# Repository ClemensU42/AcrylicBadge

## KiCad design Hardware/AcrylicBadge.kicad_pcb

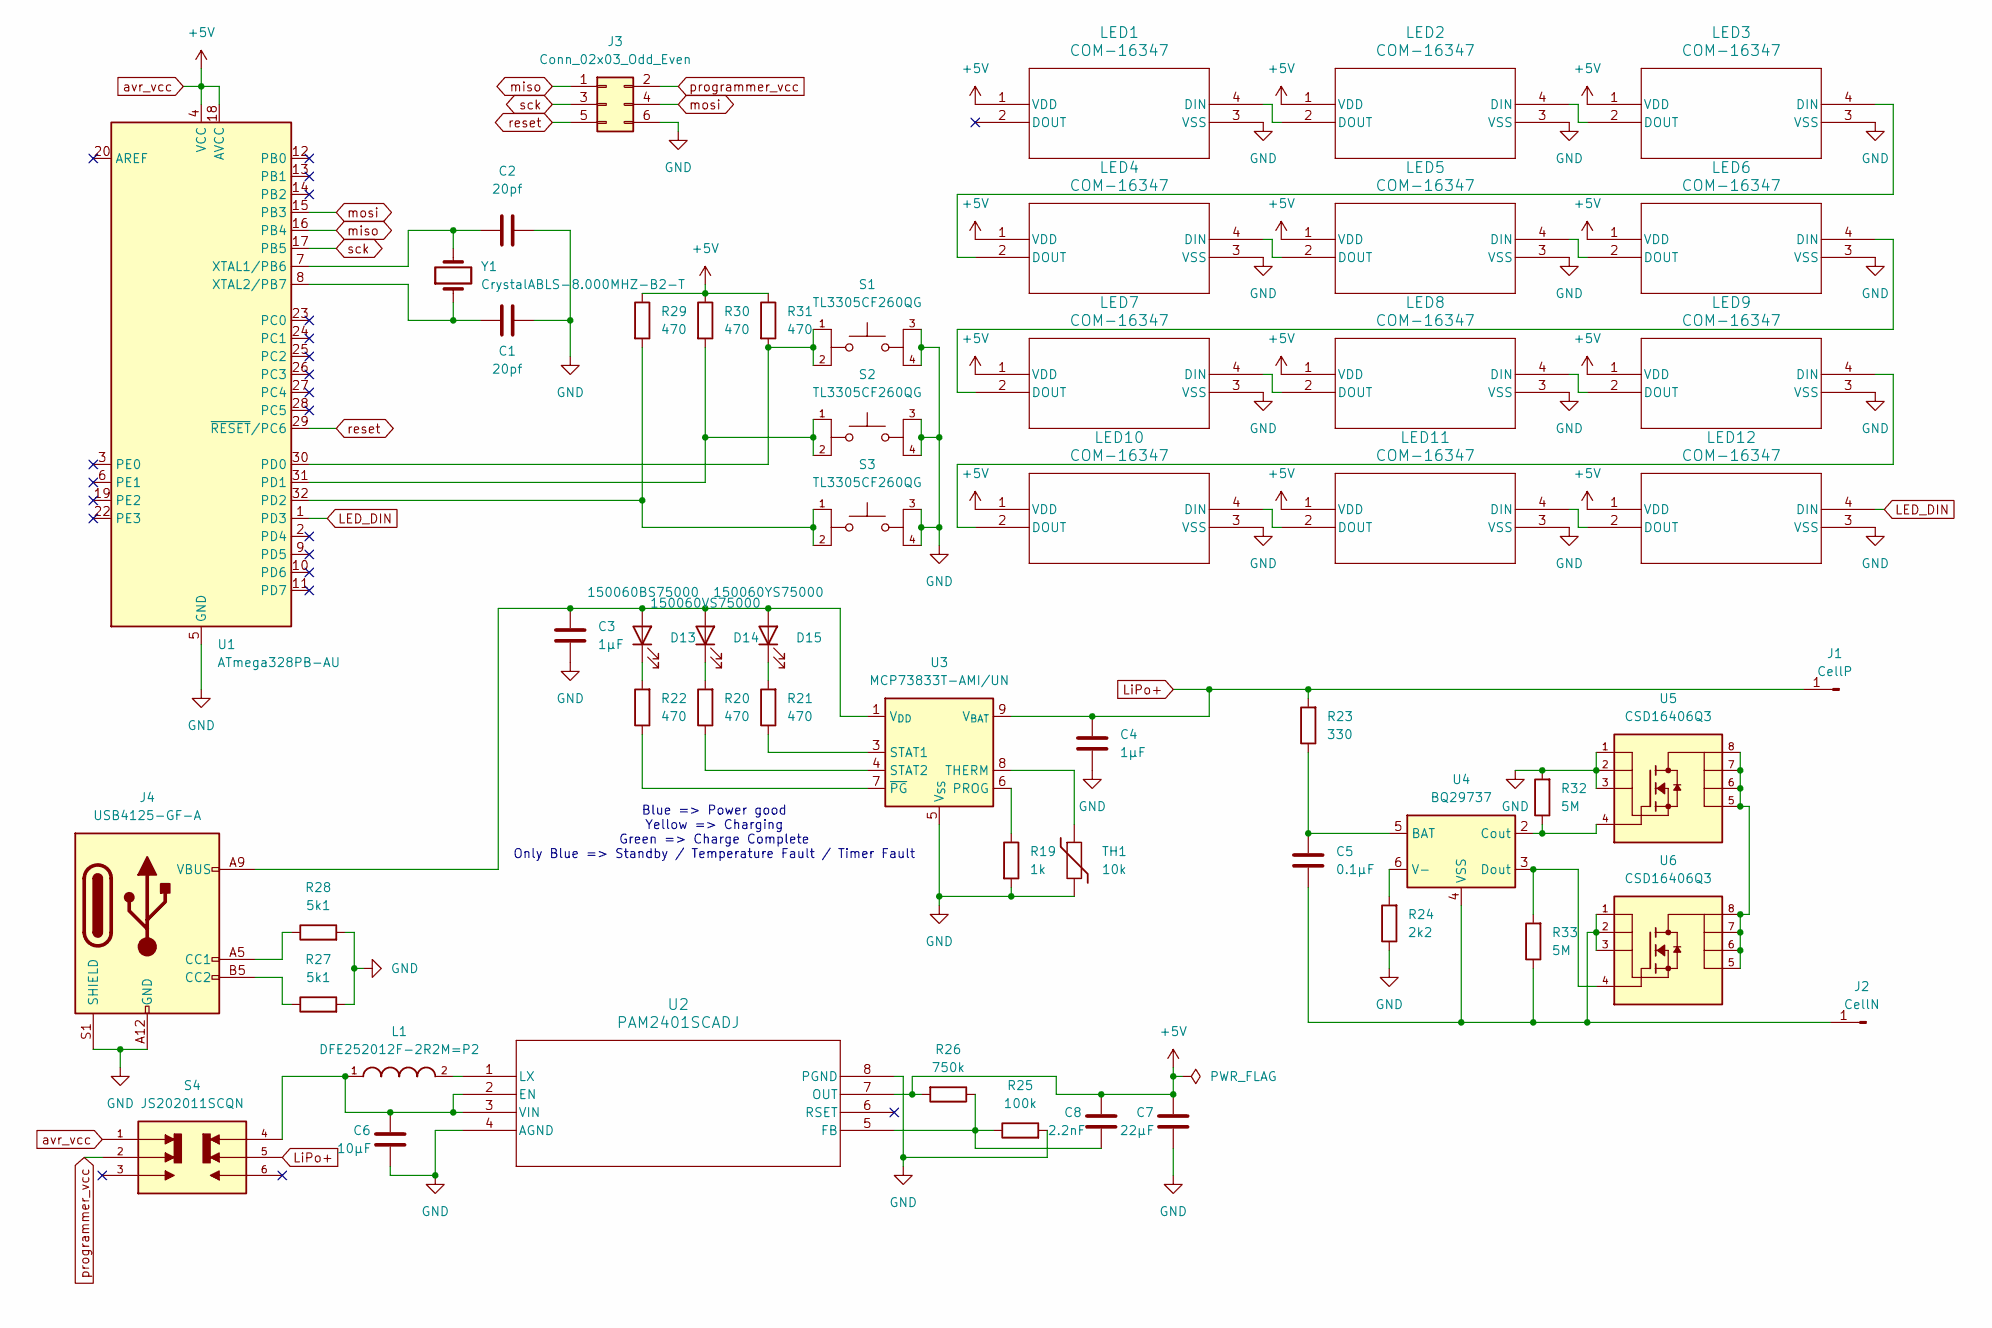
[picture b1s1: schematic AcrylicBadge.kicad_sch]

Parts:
C1, C2: 20pf; C_1206_3216Metric_Pad1.33x1.80mm_HandSolder
C3, C4: 1µF; C_1206_3216Metric_Pad1.33x1.80mm_HandSolder
C5: 0.1µF; C_1206_3216Metric_Pad1.33x1.80mm_HandSolder
C6: 10µF; C_1206_3216Metric_Pad1.33x1.80mm_HandSolder
C7: 22µF; C_1206_3216Metric_Pad1.33x1.80mm_HandSolder
C8: 2.2nF; C_1206_3216Metric_Pad1.33x1.80mm_HandSolder
D13: 150060BS75000; LED_0603_1608Metric
D14: 150060VS75000; LED_0603_1608Metric
D15: 150060YS75000; LED_0603_1608Metric
J1: CellP; SolderWire-0.75sqmm_1x01_D1.25mm_OD3.5mm
J2: CellN; SolderWire-0.75sqmm_1x01_D1.25mm_OD3.5mm
J3: Conn_02x03_Odd_Even; IDC-Header_2x03_P2.54mm_Vertical
J4: USB4125-GF-A; USB_C_Receptacle_GCT_USB4125-xx-x_6P_TopMnt_Horizontal
L1: DFE252012F-2R2M=P2; INDC2520X120N
LED1, LED2, LED3, LED4, LED5, LED6, LED7, LED8, LED9, LED10, LED11, LED12: COM-16347; COM-16347_SPK
R19: 1k; R_1206_3216Metric_Pad1.30x1.75mm_HandSolder
R20, R21, R22, R29, R30, R31: 470; R_1206_3216Metric_Pad1.30x1.75mm_HandSolder
R23: 330; R_1206_3216Metric_Pad1.30x1.75mm_HandSolder
R24: 2k2; R_1206_3216Metric_Pad1.30x1.75mm_HandSolder
R25: 100k; R_1206_3216Metric_Pad1.30x1.75mm_HandSolder
R26: 750k; R_1206_3216Metric_Pad1.30x1.75mm_HandSolder
R27, R28: 5k1; R_1206_3216Metric_Pad1.30x1.75mm_HandSolder
R32, R33: 5M; R_1206_3216Metric_Pad1.30x1.75mm_HandSolder
S1, S2, S3: TL3305CF260QG; SW_TL3305CF260QG; PARTREV C
S4: JS202011SCQN; SW_JS202011SCQN; PARTREV 26 May 22; DigiKey_Part_Number 401-2002-2-ND
TH1: 10k; R_0603_1608Metric
U1: ATmega328PB-AU; TQFP-32_7x7mm_P0.8mm
U2: PAM2401SCADJ; MSOP8_DIO
U3: MCP73833T-AMI/UN; MSOP-10_3x3mm_P0.5mm
U4: BQ29737; WSON-6_1.5x1.5mm_P0.5mm
U5, U6: CSD16406Q3; TRANS_CSD16406Q3
Y1: CrystalABLS-8.000MHZ-B2-T; Crystal_SMD_HC49-SD

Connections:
GND: C1.2, C2.2, C3.2, C4.2, C6.1, C7.1, J3.6, J4.A12 (GND), J4.B12 (GND), J4.S1 (SHIELD), LED1.3 (VSS), LED2.3 (VSS), LED3.3 (VSS), LED4.3 (VSS), LED5.3 (VSS), LED6.3 (VSS), LED7.3 (VSS), LED8.3 (VSS), LED9.3 (VSS), LED10.3 (VSS), LED11.3 (VSS), LED12.3 (VSS), R19.2, R24.1, R25.2, R27.2, R28.2, R32.2, S1.3, S1.4, S2.3, S2.4, S3.3, S3.4, TH1.2, U1.5 (GND), U1.21 (GND), U2.4 (AGND), U2.8 (PGND), U3.5 (V_{SS}), U5.1, U5.2, U5.3
LED_DIN: LED12.4 (DIN), U1.1 (PD3)
LiPo+: C4.1, J1.1, R23.2, S4.5, U3.9 (V_{BAT}), U3.10 (V_{BAT}); also elsewhere on the board
unnamed: C3.1, D13.2 (A), D14.2 (A), D15.2 (A), J4.A9 (VBUS), J4.B9 (VBUS), U3.1 (V_{DD}), U3.2 (V_{DD})
unnamed: D13.1 (K), R22.2
unnamed: D14.1 (K), R20.2
unnamed: D15.1 (K), R21.2
unnamed 7: C5.2, J2.1, R33.1, U4.4 (VSS), U6.1, U6.2, U6.3; also elsewhere on the board
unnamed: J4.A5 (CC1), R28.1
unnamed: J4.B5 (CC2), R27.1
unnamed: LED1.4 (DIN), LED2.2 (DOUT)
unnamed: LED2.4 (DIN), LED3.2 (DOUT)
unnamed: LED3.4 (DIN), LED4.2 (DOUT)
unnamed: LED4.4 (DIN), LED5.2 (DOUT)
unnamed: LED5.4 (DIN), LED6.2 (DOUT)
unnamed: LED6.4 (DIN), LED7.2 (DOUT)
unnamed: LED7.4 (DIN), LED8.2 (DOUT)
unnamed: LED8.4 (DIN), LED9.2 (DOUT)
unnamed: LED10.4 (DIN), LED11.2 (DOUT)
unnamed: LED9.4 (DIN), LED10.2 (DOUT)
unnamed: LED11.4 (DIN), LED12.2 (DOUT)
unnamed: R31.2, S1.1, S1.2, U1.30 (PD0)
unnamed: R30.2, S2.1, S2.2, U1.31 (PD1)
unnamed: R29.2, S3.1, S3.2, U1.32 (PD2)
unnamed: C2.1, U1.7 (XTAL1/PB6), Y1.2
unnamed: C1.1, U1.8 (XTAL2/PB7), Y1.1
unnamed: C6.2, L1.1, S4.4, U2.2 (EN), U2.3 (VIN)
unnamed: C8.1, R25.1, R26.1, U2.5 (FB)
unnamed: L1.2, U2.1 (LX)
unnamed: R19.1, U3.6 (PROG)
unnamed: R21.1, U3.3 (STAT1)
unnamed: R20.1, U3.4 (STAT2)
unnamed: TH1.1, U3.8 (THERM)
unnamed: R22.1, U3.7 (~PG)
unnamed: C5.1, R23.1, U4.5 (BAT)
unnamed: R32.1, U4.2 (Cout), U5.4
unnamed: R33.2, U4.3 (Dout), U6.4
unnamed: R24.2, U4.6 (V-)
unnamed: U5.5, U5.6, U5.7, U5.8, U6.5, U6.6, U6.7, U6.8
avr_vcc: C7.2, C8.2, LED1.1 (VDD), LED2.1 (VDD), LED3.1 (VDD), LED4.1 (VDD), LED5.1 (VDD), LED6.1 (VDD), LED7.1 (VDD), LED8.1 (VDD), LED9.1 (VDD), LED10.1 (VDD), LED11.1 (VDD), LED12.1 (VDD), R26.2, R29.1, R30.1, R31.1, S4.1, U1.4 (VCC), U1.18 (AVCC), U2.7 (OUT)
miso: J3.1, U1.16 (PB4)
mosi: J3.4, U1.15 (PB3)
programmer_vcc: J3.2, S4.2
reset: J3.5, U1.29 (~RESET/PC6)
sck: J3.3, U1.17 (PB5)

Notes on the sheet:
Blue => Power good Yellow => Charging Green => Charge Complete Only Blue => Standby / Temperature Fault / Timer Fault

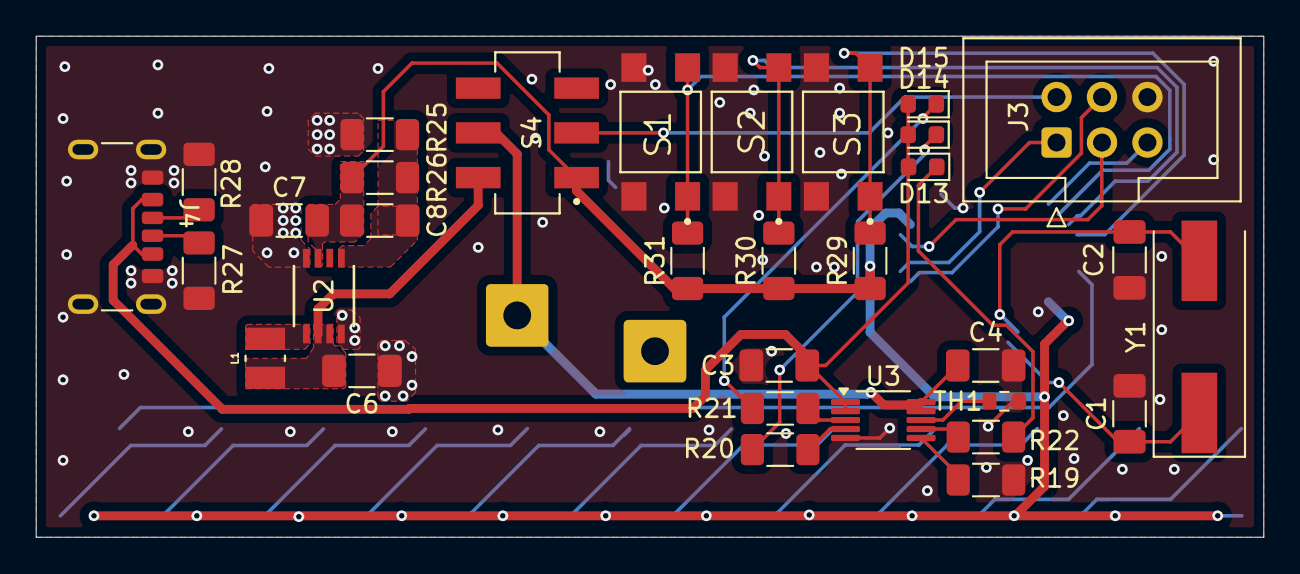
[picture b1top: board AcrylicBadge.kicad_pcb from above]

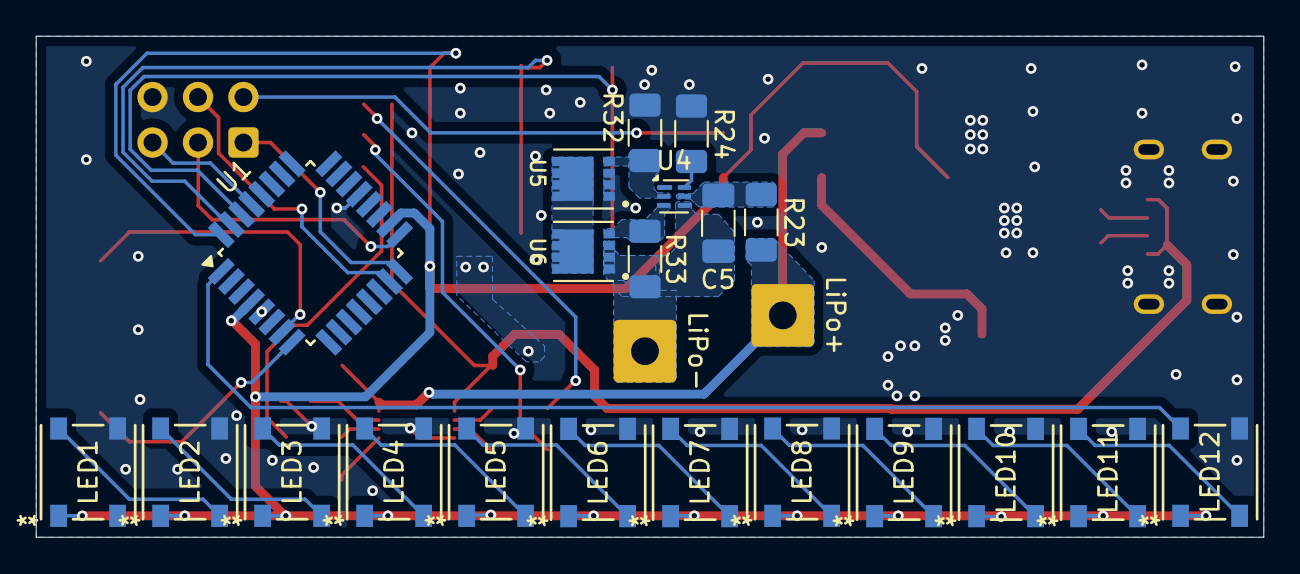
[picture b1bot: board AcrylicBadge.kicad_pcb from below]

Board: 2 copper layers, 68.6 x 28.0 mm, 55 parts (23 on the bottom side), 45 nets.

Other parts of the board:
LiPo+: CellP; SolderWire-0.75sqmm_1x01_D1.25mm_OD3.5mm
LiPo-: CellN; SolderWire-0.75sqmm_1x01_D1.25mm_OD3.5mm

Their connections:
LiPo+: LiPo+.1; also elsewhere on the board
unnamed 7: LiPo-.1; also elsewhere on the board

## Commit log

2025-02-15 Created repository
2025-02-17 Started PCB Layout
2025-02-20 Finished PCB layout
2025-02-20 Added FreeCad Project for Case
2025-02-21 Added measurements
